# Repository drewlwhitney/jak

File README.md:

# Just Another Keyboard
It's Just Another Keyboard that amalgamates the [Corne](github.com/foostan/crkbd), [Ferris Sweep](https://github.com/davidphilipbarr/Sweep), and [Fifi](https://github.com/raychengy/fifi_split_keeb).

Wired | Wireless
-|-
 | 
<sub>Fully assembled wired version with keycaps from Nuphy</sub> | <sub>Fully assembled wireless version

## Notable Features
- Designed for [Gateron KS-33 Low Profile Switches](https://www.gateron.co/products/gateron-low-profile-mechanical-switch-set) with hotswap sockets

- Uses the [Seeed Studio XIAO microcontroller](https://www.seeedstudio.com/XIAO-RP2040-v1-0-p-5026.html) with either the [RP2040](https://www.seeedstudio.com/XIAO-RP2040-v1-0-p-5026.html) variant (for wired builds) or the [XIAO-BLE](https://www.seeedstudio.com/Seeed-XIAO-BLE-nRF52840-p-5201.html) variant (for wireless builds)

- 2-pin JST connector for the battery in wireless builds

- USB-C full duplex USART communication for wired builds. None of that [TRRS nonesense](https://gabevenberg.com/posts/stop-using-trrs/)!

- [Switch plates](./switch-plate/) you can order with the PCB

- [3D printable cases](./case/) that exactly fit the boards with a battery or USB-C connectors

## Build Guide
Refer to the [Build Guide](./docs/build_guide.md).

## Firmware Guide
### ZMK
You can use ZMK with *either* the wired or wireless version of the keyboard.

- Follow the [usual setup steps for ZMK](https://zmk.dev/docs/user-setup).

- Add the `zmk-keyboards-jak` module by following the instructions on the [module's GitHub](https://github.com/drewlwhitney/zmk-keyboards-jak).

- For wired builds, follow the extra steps on the [module's GitHub](https://github.com/drewlwhitney/zmk-keyboards-jak).

- Build and flash the firmware.

### QMK
You can use QMK with the **wired version only**.

- Follow the [usual setup steps for QMK](https://docs.qmk.fm/newbs).

- Clone the [keyboard description repo](https://github.com/drewlwhitney/qmk-keyboards-jak) into your `qmk_firmware/keyboards` folder and rename it to `"jak"`.[^1]

- Follow the build instructions from the [keyboard description repo](https://github.com/drewlwhitney/qmk-keyboards-jak).

[^1]: If there is a better way to do this, please open an issue to let me know!

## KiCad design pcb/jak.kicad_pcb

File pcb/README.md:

## PCB
The PCB is non-reversible and is designed for Gateron KS-33 Low Profile Switches with hotswap sockets.

<sub>Front</sub>

<sub>Back</sub>

## Ordering
This was written on January 7, 2026 for [JLCPCB](https://jlcpcb.com/).

Upload the [PCB Gerber Files (.zip)](./gerbers/) to [JLCPCB](https://cart.jlcpcb.com/quote), then leave everything as-is except for:

| Option | Value |
| -- | -- |
| Different Design | 2 |
| PCB Color | Your choice |

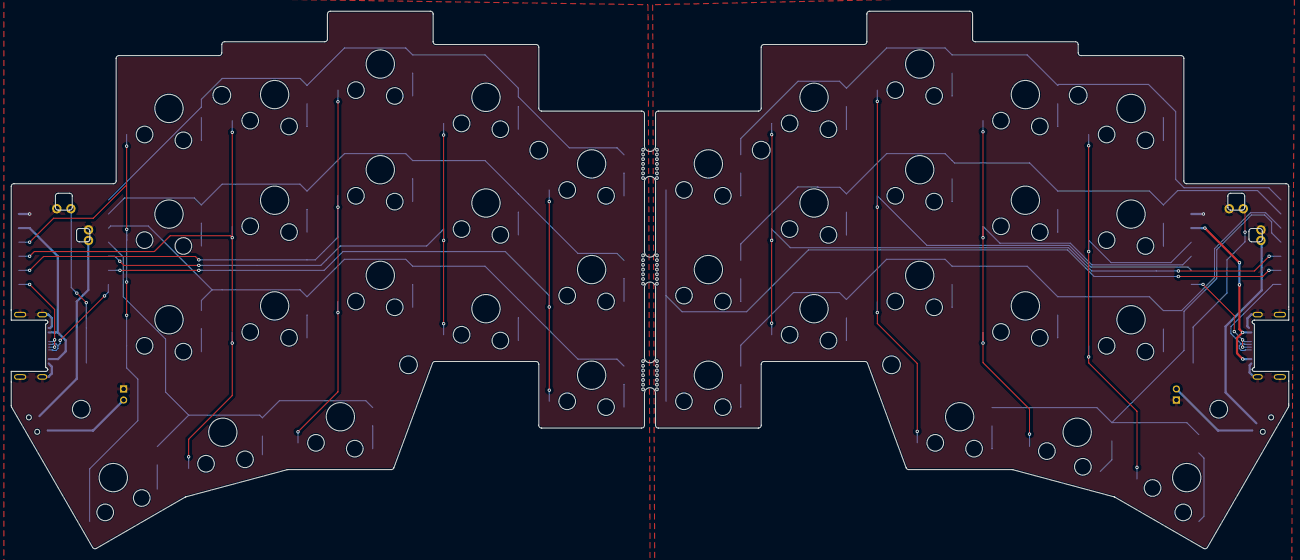
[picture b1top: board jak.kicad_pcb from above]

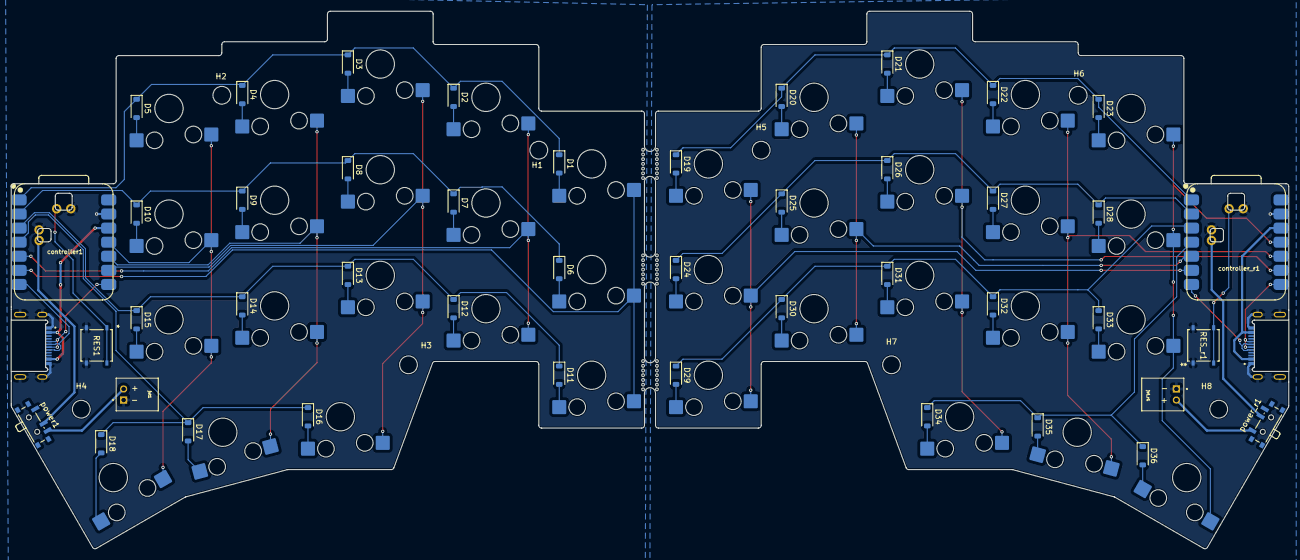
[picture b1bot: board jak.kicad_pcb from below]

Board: 2 copper layers, 230.3 x 96.9 mm, 90 parts (82 on the bottom side), 68 nets.

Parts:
D1, D2, D3, D4, D5, D6, D7, D8, D9, D10, D11, D12, D13, D14, D15, D16, D17, D18, D19, D20, D21, D22, D23, D24, D25, D26, D27, D28, D29, D30, D31, D32, D33, D34, D35, D36: 1N4148W; D_SOD-123
H1, H2, H3, H4, H5, H6, H7, H8: MountingHole; MountingHole_3.2mm_M3
RES1: PTS526 SM15 SMTR2 LFS; SON4_PTS526 SM15 SMTR2 LFS_CNK
RES_r1: PTS526 SM15 SMTR2 LFS; SON4_PTS526 SM15 SMTR2 LFS_CNK
SW1, SW1_r1, SW2, SW2_r1, SW3, SW3_r1, SW4, SW4_r1, SW5, SW5_r1, SW6, SW6_r1, SW7, SW7_r1, SW8, SW8_r1, SW9, SW9_r1, SW10, SW10_r1, SW11, SW11_r1, SW12, SW12_r1, SW13, SW13_r1, SW14, SW14_r1, SW15, SW15_r1, SW16, SW16_r1, SW17, SW17_r1, SW18, SW18_r1: SW_Push; Gateron-KS33-Hotswap-1U
controller1: XIAO-nRF52840-SMD; XIAO-nRF52840-SMD-underside
controller_r1: XIAO-nRF52840-SMD; XIAO-nRF52840-SMD-underside
jst1: Conn_01x02; JST_S2B-PH-K-S_LF__SN_
jst_r1: S2B-PH-K-S_LF__SN_; JST_S2B-PH-K-S_LF__SN_
power1: SW_SPDT; SW_SPDT_PCM12
power_r1: SW_SPDT; SW_SPDT_PCM12
split_connector1: USB_C_Receptacle_USB2.0_14P; GCT_USB4505-03-0-A_REVA
split_connector_r1: USB_C_Receptacle_USB2.0_14P; GCT_USB4505-03-0-A_REVA

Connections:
GND: RES1.3, RES1.4, controller1.13 (GND), controller1.16 (GND), controller1.22 (GND), jst1.1, split_connector1.A1_B12 (GND_A), split_connector1.B1_A12 (GND_B), split_connector1.S1 (SHELL_GND), split_connector1.S2 (SHELL_GND), split_connector1.S3 (SHELL_GND), split_connector1.S4 (SHELL_GND)
GND_r: RES_r1.1, RES_r1.2, controller_r1.13 (GND), controller_r1.16 (GND), controller_r1.22 (GND), jst_r1.1, split_connector_r1.A1_B12 (GND_A), split_connector_r1.B1_A12 (GND_B), split_connector_r1.S1 (SHELL_GND), split_connector_r1.S2 (SHELL_GND), split_connector_r1.S3 (SHELL_GND), split_connector_r1.S4 (SHELL_GND)
unnamed: D1.2 (A), SW1.2
unnamed: D2.2 (A), SW2.2
unnamed: D3.2 (A), SW3.2
unnamed: D4.2 (A), SW4.2
unnamed: D5.2 (A), SW5.2
unnamed: D6.2 (A), SW6.2
unnamed: D7.2 (A), SW7.2
unnamed: D8.2 (A), SW8.2
unnamed: D9.2 (A), SW9.2
unnamed: D10.2 (A), SW10.2
unnamed: D11.2 (A), SW11.2
unnamed: D12.2 (A), SW12.2
unnamed: D13.2 (A), SW13.2
unnamed: D14.2 (A), SW14.2
unnamed: D15.2 (A), SW15.2
unnamed: D16.2 (A), SW16.2
unnamed: D17.2 (A), SW17.2
unnamed: D18.2 (A), SW18.2
unnamed: D19.2 (A), SW1_r1.2
unnamed: D20.2 (A), SW2_r1.2
unnamed: D21.2 (A), SW3_r1.2
unnamed: D22.2 (A), SW4_r1.2
unnamed: D23.2 (A), SW5_r1.2
unnamed: D24.2 (A), SW6_r1.2
unnamed: D25.2 (A), SW7_r1.2
unnamed: D26.2 (A), SW8_r1.2
unnamed: D27.2 (A), SW9_r1.2
unnamed: D28.2 (A), SW10_r1.2
unnamed: D29.2 (A), SW11_r1.2
unnamed: D30.2 (A), SW12_r1.2
unnamed: D31.2 (A), SW13_r1.2
unnamed: D32.2 (A), SW14_r1.2
unnamed: D33.2 (A), SW15_r1.2
unnamed: D34.2 (A), SW16_r1.2
unnamed: D35.2 (A), SW17_r1.2
unnamed: D36.2 (A), SW18_r1.2
VCC: controller1.12 (3V3), split_connector1.A4_B9 (VBUS_A), split_connector1.B4_A9 (VBUS_B)
VCC_r: controller_r1.12 (3V3), split_connector_r1.A4_B9 (VBUS_A), split_connector_r1.B4_A9 (VBUS_B)
battery+: jst1.2, power1.3 (C)
battery+_r: jst_r1.2, power_r1.1 (A)
battery_switched: controller1.15 (BAT), power1.2 (B)
battery_switched_r: controller_r1.15 (BAT), power_r1.2 (B)
col0: SW1.1, SW6.1, SW11.1, controller1.6 (P0.05_A5_D5_SCL)
col0_r: SW1_r1.1, SW6_r1.1, SW11_r1.1, controller_r1.6 (P0.05_A5_D5_SCL)
col1: SW2.1, SW7.1, SW12.1, controller1.5 (P0.04_A4_D4_SDA)
col1_r: SW2_r1.1, SW7_r1.1, SW12_r1.1, controller_r1.5 (P0.04_A4_D4_SDA)
col2: SW3.1, SW8.1, SW13.1, SW16.1, controller1.9 (P1.13_D8_SCK)
col2_r: SW3_r1.1, SW8_r1.1, SW13_r1.1, SW16_r1.1, controller_r1.9 (P1.13_D8_SCK)
col3: SW4.1, SW9.1, SW14.1, SW17.1, controller1.10 (P1.14_D9_MISO)
col3_r: SW4_r1.1, SW9_r1.1, SW14_r1.1, SW17_r1.1, controller_r1.10 (P1.14_D9_MISO)
col4: SW5.1, SW10.1, SW15.1, SW18.1, controller1.11 (P1.15_D10_MOSI)
col4_r: SW5_r1.1, SW10_r1.1, SW15_r1.1, SW18_r1.1, controller_r1.11 (P1.15_D10_MOSI)
reset: RES1.1, RES1.2, controller1.21 (RESET)
reset_r: RES_r1.3, RES_r1.4, controller_r1.21 (RESET)
row0: D1.1 (K), D2.1 (K), D3.1 (K), D4.1 (K), D5.1 (K), controller1.1 (P0.02_A0_D0)
row0_r: D19.1 (K), D20.1 (K), D21.1 (K), D22.1 (K), D23.1 (K), controller_r1.1 (P0.02_A0_D0)
row1: D6.1 (K), D7.1 (K), D8.1 (K), D9.1 (K), D10.1 (K), controller1.2 (P0.03_A1_D1)
row1_r: D24.1 (K), D25.1 (K), D26.1 (K), D27.1 (K), D28.1 (K), controller_r1.2 (P0.03_A1_D1)
row2: D11.1 (K), D12.1 (K), D13.1 (K), D14.1 (K), D15.1 (K), controller1.3 (P0.28_A2_D2)
row2_r: D29.1 (K), D30.1 (K), D31.1 (K), D32.1 (K), D33.1 (K), controller_r1.3 (P0.28_A2_D2)
row3: D16.1 (K), D17.1 (K), D18.1 (K), controller1.4 (P0.29_A3_D3)
row3_r: D34.1 (K), D35.1 (K), D36.1 (K), controller_r1.4 (P0.29_A3_D3)
split_comms+: controller1.7 (P1.11_D6_TX), split_connector1.A6 (DP1), split_connector1.B6 (DP2)
split_comms+_r: controller_r1.8 (P1.12_D7_RX), split_connector_r1.A6 (DP1), split_connector_r1.B6 (DP2)
split_comms-: controller1.8 (P1.12_D7_RX), split_connector1.A7 (DN1), split_connector1.B7 (DN2)
split_comms-_r: controller_r1.7 (P1.11_D6_TX), split_connector_r1.A7 (DN1), split_connector_r1.B7 (DN2)

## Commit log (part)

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2026-01-07 Added images
2026-01-07 Replaced the through-hole surface USB-C connector with a flush one
2026-01-07 Added a 3D printable case
2026-01-07 Updated section of README
2026-01-08 Fixed the submodule issus for the symbol and footprint libraries
2026-01-08 Forgot files
2026-01-08 Updated README and added READMEs for the PCB, switch plate, and case. Added a build guide with bill of materials
2026-01-08 Removed lockfiles
2026-01-08 Fix typo in README for case files description
2026-01-08 Update description of nice!nanos in build guide
2026-01-13 Added an initial attempt at QMK support
2026-01-20 In the process of transitioning the board to use the SEEED XIAO instead of a pro micro
2026-01-23 Made some final changes to the pcb and split the switch plate into two versions to allow metal decorations
2026-01-23 Updated the README
2026-01-23 Corrected the README
2026-01-23 Fixed switch plate README
2026-01-23 Fixed PCB README
2026-01-23 Updated build guide
2026-01-26 Making sure we're up to date
2026-01-26 Clarify diode orientation for soldering PCB
    Added note about diode orientation during soldering.
2026-01-27 Modified the pcb to have stronger mousebites
2026-01-28 Updated the case and split it into wired and wireless variants
2026-01-28 Updated the build guide and case README to specify the M2 screw length
2026-02-23 Updated the cases to better brace the outer PCB edges
2026-02-23 Fixed the footprint for the reset switch, as it was wrong on the website I got it from
2026-02-28 Fixed the power switch pins being swapped and updated the gerber files
2026-03-24 Revert "Fixed the power switch pins being swapped and updated the gerber files"
    This reverts commit 317bf88c69a0fc961124c453349158f4046b94f1.
2026-03-24 Reverted the power switch fix, I actually like this mode
2026-03-24 Updated the gerbers
2026-03-24 Removed some backups
2026-03-24 Updated QMK README
2026-03-24 Updated the build guide
2026-03-24 Updated stuff after building the wireless version
2026-03-24 Updated the case pictures
2026-05-14 Fixed the wired case and updates the qmk stuff
2026-05-15 iesrtniesn
2026-05-15 Removed a commented config setting for QMK
2026-05-15 Moved the QMK stuff to it's own repo
2026-05-15 Updated the docs for the wired version!
2026-05-15 Removed the TODO
2026-05-15 Made the pictures render side-by-side to save a bit of screen space
2026-05-15 Added a link on the Seeed Studio XIAO
2026-05-15 Removed some code text
